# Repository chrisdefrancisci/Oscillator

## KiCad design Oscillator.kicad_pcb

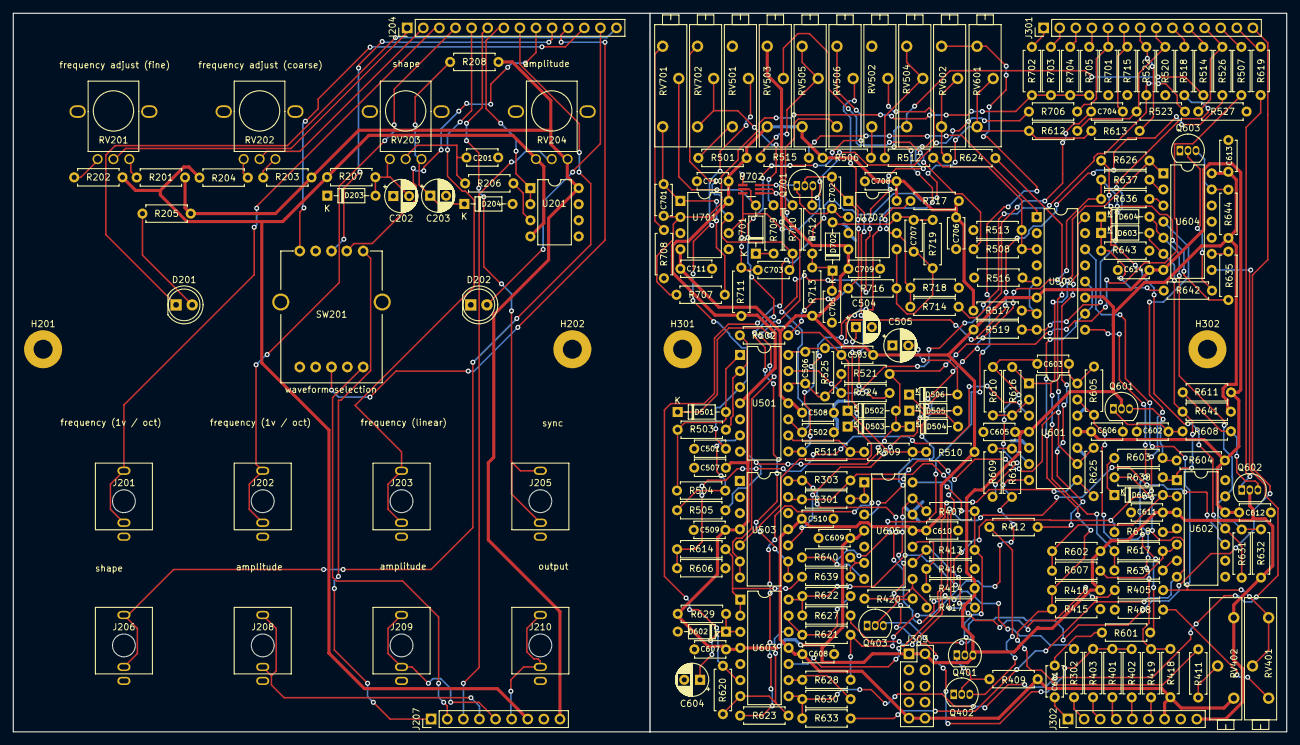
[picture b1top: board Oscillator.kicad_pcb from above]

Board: 2 copper layers, 200.9 x 113.3 mm, 226 parts (0 on the bottom side), 157 nets.

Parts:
C201, C501, C502: .1u; C_Disc_D4.7mm_W2.5mm_P5.00mm
C202, C203, C504, C505, C604: 1u; CP_Radial_D5.0mm_P2.50mm
C503: 0.002u; C_Disc_D4.7mm_W2.5mm_P5.00mm
C506: 10p; C_Disc_D4.7mm_W2.5mm_P5.00mm
C507, C508, C509, C510, C602, C605, C606, C607, C608, C609, C610, C611, C612, C613, C614, C706, C708, C709, C710, C711: 0.1u; C_Disc_D4.7mm_W2.5mm_P5.00mm
C601, C603: 10u; C_Disc_D4.7mm_W2.5mm_P5.00mm
C701, C703, C705: 100p; C_Disc_D4.7mm_W2.5mm_P5.00mm
C702: 0.005u; C_Disc_D4.7mm_W2.5mm_P5.00mm
C704: 0.001u; C_Disc_D4.7mm_W2.5mm_P5.00mm
C707: 4.7p; C_Disc_D4.7mm_W2.5mm_P5.00mm
D201, D202: LED; LED_D5.0mm
D203, D204: NZX5V1B; D_DO-35_SOD27_P7.62mm_Horizontal
D501, D502, D503, D504, D505, D506, D601, D603, D604, D701, D702: D; D_DO-35_SOD27_P7.62mm_Horizontal
D602: BZX55C10; D_DO-35_SOD27_P7.62mm_Horizontal
H201, H202, H301, H302: MountingHole; MountingHole_3mm_Pad
J201, J202, J203, J205, J206, J208, J209, J210: AudioJack2; A-2563
J204, J301: Conn_01x14; PinHeader_1x14_P2.54mm_Vertical
J207, J302: Conn_01x09; PinHeader_1x09_P2.54mm_Vertical
J303: Conn_02x05_Odd_Even; PinHeader_2x05_P2.54mm_Vertical
Q401, Q403, Q603: 2N3904; TO-92_Inline
Q402: 2N3906; TO-92_Inline
Q601, Q602, Q701: Q_NJFET_DSG; TO-92_Inline
R201, R202, R605, R614: 200k; R_Axial_DIN0207_L6.3mm_D2.5mm_P7.62mm_Horizontal
R203, R415, R503, R617, R618, R633, R634, R643: 47k; R_Axial_DIN0207_L6.3mm_D2.5mm_P7.62mm_Horizontal
R204, R206, R207, R208, R502, R504, R505, R506, R509, R522, R523, R524, R602, R626, R627, R629, R632, R639, R640, R641, R644, R710, R716, R717: 10k; R_Axial_DIN0207_L6.3mm_D2.5mm_P7.62mm_Horizontal
R205, R416, R419, R507, R513, R514, R518, R714: 1k; R_Axial_DIN0207_L6.3mm_D2.5mm_P7.62mm_Horizontal
R301, R302, R303, R401, R402, R403, R405, R414, R417, R420, R501, R515, R520, R521, R601, R609, R612, R615, R623, R624, R625, R635, R636, R637, R701, R703, R704, R705, R712, R715: 100k; R_Axial_DIN0207_L6.3mm_D2.5mm_P7.62mm_Horizontal
R407, R413, R707, R718: 2k; R_Axial_DIN0207_L6.3mm_D2.5mm_P7.62mm_Horizontal
R408: 150; R_Axial_DIN0207_L6.3mm_D2.5mm_P7.62mm_Horizontal
R409, R610, R613, R621, R628: 120k; R_Axial_DIN0207_L6.3mm_D2.5mm_P7.62mm_Horizontal
R410, R508: 470k; R_Axial_DIN0207_L6.3mm_D2.5mm_P7.62mm_Horizontal
R411: 2M; R_Axial_DIN0207_L6.3mm_D2.5mm_P7.62mm_Horizontal
R412, R510, R511, R512, R603, R608, R642: 20k; R_Axial_DIN0207_L6.3mm_D2.5mm_P7.62mm_Horizontal
R418, R519, R526, R709: 4.7k; R_Axial_DIN0207_L6.3mm_D2.5mm_P7.62mm_Horizontal
R516: 130k; R_Axial_DIN0207_L6.3mm_D2.5mm_P7.62mm_Horizontal
R517, R604, R611, R702, R706, R711, R719: 1M; R_Axial_DIN0207_L6.3mm_D2.5mm_P7.62mm_Horizontal
R525: 10M; R_Axial_DIN0207_L6.3mm_D2.5mm_P7.62mm_Horizontal
R527, R619: 3k; R_Axial_DIN0207_L6.3mm_D2.5mm_P7.62mm_Horizontal
R606: 180k; R_Axial_DIN0207_L6.3mm_D2.5mm_P7.62mm_Horizontal
R607, R631, R638: 3M; R_Axial_DIN0207_L6.3mm_D2.5mm_P7.62mm_Horizontal
R616, R622, R630: 39k; R_Axial_DIN0207_L6.3mm_D2.5mm_P7.62mm_Horizontal
R620: 33k; R_Axial_DIN0207_L6.3mm_D2.5mm_P7.62mm_Horizontal
R708: 475; R_Axial_DIN0207_L6.3mm_D2.5mm_P7.62mm_Horizontal
R713: 18k; R_Axial_DIN0207_L6.3mm_D2.5mm_P7.62mm_Horizontal
RV201, RV202, RV203, RV204: 100k; A-5513
RV401: 2k; Potentiometer_Bourns_3006P_Horizontal
RV402, RV503, RV504, RV506, RV601, RV602, RV702: 100k; Potentiometer_Bourns_3006P_Horizontal
RV501, RV502: 10k; Potentiometer_Bourns_3006P_Horizontal
RV505: 1M; Potentiometer_Bourns_3006P_Horizontal
RV701: 100; Potentiometer_Bourns_3006P_Horizontal
SW201: SR1712F-0204-20F0A-N9-N-027
U201, U703: TL072; DIP-8_W7.62mm
U501, U503, U601, U603, U605: TL074; DIP-14_W7.62mm
U502: LM13700; DIP-16_W7.62mm
U602: LM339; DIP-14_W7.62mm
U604: 4066; DIP-14_W7.62mm
U701: OP275; DIP-8_W7.62mm
U702: DMMT3904W; SOT-363_SC-70-6_Handsoldering

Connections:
+12V: C507.1, C509.1, C605.1, C607.1, C609.1, C611.1, C613.1, C706.1, C708.1, C710.1, J207.9, J302.9, J303.1, J303.2, Q401.3, Q601.2, Q602.2, R201.1, R203.1, R205.1, R208.2, R410.2, R414.2, R501.1, R506.1, R517.2, R602.2, R629.1, R632.2, R641.2, R644.2, R711.1, R717.1, RV204.3, RV402.1, RV503.1, RV505.1, U201.8, U501.4, U502.11, U503.4, U601.4, U602.3, U603.4, U604.14, U605.4, U701.8, U703.8
-12V: C503.1, C508.2, C510.2, C606.2, C608.2, C610.2, C612.2, C614.2, C709.2, C711.2, J207.7, J302.7, J303.9, J303.10, R202.2, R204.2, R207.2, R409.2, R418.2, R510.1, R519.1, R604.2, R611.1, R713.2, RV204.1, RV402.3, RV503.3, U201.4, U501.11, U502.6, U503.11, U601.11, U602.12, U603.11, U604.7, U605.11, U701.4, U703.4
/main/VCA/CV1: J302.4, R401.2
/main/VCA/CV2: J302.5, R402.2
/main/VCA/IN: R303.1, R405.2, U503.14
/main/VCA/LED: J301.14, Q403.3
/main/VCA/OFFSET: J302.3, R403.2
/main/VCA/OUT: J302.6, R419.1
/main/VCO_RAW/CV1: J301.3, R704.2
/main/VCO_RAW/CV2: J301.4, R705.2
/main/VCO_RAW/CV_LIN: J301.5, R701.1, R706.2
/main/VCO_RAW/OFFSET_COURSE: J301.2, R703.2
/main/VCO_RAW/OFFSET_FINE: J301.1, R702.2
/main/VCO_RAW/RAW: C702.1, Q701.2, R502.2, R716.2, U703.1
/main/VCO_RAW/SYNC_IN: C704.2, J301.6, R715.1
/main/VCO_SHAPE/CV: J301.8, R520.1, R523.2, R612.2
/main/VCO_SHAPE/RAMP: J301.12, R507.1
/main/VCO_SHAPE/SHAPE: J301.7, R522.2, R613.2
/main/VCO_SHAPE/SINE: J301.9, R518.1
/main/VCO_SHAPE/SQUARE: J301.11, R526.2, R527.1
/main/VCO_SHAPE/TRIANGLE: J301.10, R514.1
/main/WAVESHAPER/10v: R614.1, R639.2, U603.1, U603.2
/main/WAVESHAPER/-10v: R640.1, RV601.3, RV602.3, U605.7
/main/WAVESHAPER/High_bias_signal: R618.1, R622.1, R627.2, U603.14, U604.4
/main/WAVESHAPER/IN: C601.2, J302.1
/main/WAVESHAPER/LED: J301.13, R619.1
/main/WAVESHAPER/Low_bias_signal: R630.1, R633.2, U603.8, U604.8
/main/WAVESHAPER/Mid_bias_signal: R616.1, R617.1, R626.2, R634.2, U601.1, U604.1
/main/WAVESHAPER/OUT: R301.2, U605.1, U605.2
/panel/fm_cv1: J201.T, J204.3
/panel/fm_cv2: J202.T, J204.4
/panel/fm_cv_lin: J203.T, J204.5
/panel/fold_led: D202.2, J204.13
/panel/freq_adj_course: J204.2, RV202.2
/panel/freq_adj_fine: J204.1, RV201.2
/panel/out: J207.6, J210.T
/panel/ramp: J204.12, SW201.6
/panel/shape_cv: J204.8, J206.T
/panel/shape_offset: J204.7, U201.1, U201.2
/panel/sine: J204.9, SW201.9
/panel/square: J204.11, SW201.3
/panel/sync: J204.6, J205.T
/panel/tri: J204.10, SW201.8
/panel/vca_cv1: J207.4, J208.T
/panel/vca_cv2: J207.5, J209.T
/panel/vca_led: D201.1, J204.14
/panel/vca_offset: J207.3, RV204.2
/panel/waveshaper_bypass: J207.2, SW201.1
/panel/waveshaper_in: J207.1, SW201.10
GND: C201.2, C202.1, C203.2, C501.2, C502.2, C504.2, C505.1, C507.2, C508.1, C509.2, C510.1, C602.1, C604.2, C605.2, C606.1, C607.2, C608.1, C609.2, C610.1, C611.2, C612.1, C613.2, C614.1, C705.2, C706.2, C708.2, C709.1, C710.2, C711.1, D202.1, D203.1, D204.2, D602.2, J201.S, J202.S, J203.S, J205.S, J206.S, J207.8, J208.S, J209.S, J210.S, J302.8, J303.3, J303.4, J303.5, J303.6, J303.7, J303.8, Q402.1, Q403.1, Q603.1, R408.2, R415.1, R416.1, R513.2, R516.2, R520.2, R527.2, R606.2, R643.1, R701.2, R708.1, R715.2, R718.1, RV501.3, RV502.3, SW201.2, SW201.4, SW201.5, SW201.7, U501.5, U502.4, U502.13, U503.12, U601.5, U601.10, U601.12, U603.5, U605.5, U605.12, U701.3, U701.5, U702.1, U703.3
unnamed: C201.1, R206.2, RV203.2
unnamed: C202.2, D203.2, R207.1, RV203.1
unnamed: C203.1, D204.1, R208.1, RV203.3
unnamed: C501.1, RV501.2, U501.3
unnamed: C502.1, RV502.2, U501.10
unnamed: C503.2, D501.1, D502.1, R509.2, R510.2
unnamed: C504.1, D503.1, U503.5
unnamed: C505.2, D506.2, U503.10
unnamed: C506.1, R525.1, R526.1, U501.14
unnamed: C506.2, R521.1, R525.2, U501.12
unnamed: C601.1, R601.2
unnamed: C602.2, Q601.1, R608.2
unnamed: C603.1, R609.2, R610.2
unnamed: C603.2, R605.1, U601.14
unnamed: C604.1, D602.1, R629.2, U603.3
unnamed: C701.1, R707.1, RV701.1, U701.1
unnamed: C701.2, R702.1, R703.1, R704.1, R705.1, R707.2, U701.2
unnamed: C702.2, Q701.1, U702.6, U703.2
unnamed: C703.1, R710.1, RV702.3, U701.7
unnamed: C703.2, R706.1, R711.2, U701.6, U702.3
unnamed: C704.1, R714.2
unnamed: C705.1, D702.1, R712.1, R713.1
unnamed: C707.1, D702.2, R719.1, U703.7
unnamed: C707.2, R716.1, R719.2, U703.5
unnamed: D201.2, R205.2
unnamed: D501.2, R503.1, R504.1, U501.1
unnamed: D502.2, D503.2, D504.1, R505.1, R507.2, R521.2, U501.7
unnamed: D504.2, D505.1
unnamed: D505.2, D506.1
unnamed: D601.1, R603.1
unnamed: D601.2, R602.1, R607.2, U602.2
unnamed: D603.1, D604.1, R642.1, R643.2
unnamed: D603.2, R638.1, R641.1, U602.1, U604.6
unnamed: D604.2, R631.1, R632.1, U602.13, U604.5
unnamed: D701.1, R709.2
unnamed: D701.2, RV701.2, U702.2
unnamed: J302.2, R302.2
unnamed: Q401.1, Q402.2, R409.1
unnamed: Q401.2, R407.1, R413.2, U605.14
unnamed: Q402.3, R412.1
unnamed: Q403.2, R420.1
unnamed: Q601.3, R603.2, R604.1
unnamed: Q602.1, R619.2
unnamed: Q602.3, R608.1, R611.2
unnamed: Q603.2, R642.2
unnamed: Q603.3, R644.1, U604.13
unnamed: Q701.3, R712.2
unnamed: R201.2, RV201.3
unnamed: R202.1, RV201.1
unnamed: R203.2, RV202.3
unnamed: R204.1, RV202.1
unnamed: R206.1, U201.3
unnamed: R301.1, R302.1, R303.2, U503.13
unnamed: R401.1, R402.1, R403.1, R407.2, U605.13
unnamed: R405.1, RV401.1, RV401.2, U502.14
unnamed: R408.1, RV401.3
unnamed: R410.1, R411.1, R415.2, U502.10, U502.12
unnamed: R411.2, RV402.2
unnamed: R412.2, U502.16
unnamed: R413.1, R417.2, U605.9
unnamed: R414.1, R416.2, U605.10
unnamed: R417.1, R420.2, U605.8
unnamed: R418.1, R419.2, U502.9
unnamed: R501.2, RV501.1
unnamed: R502.1, R503.2, U501.2
unnamed: R504.2, R505.2, U501.6
unnamed: R506.2, RV502.1
unnamed: R508.1, RV503.2
unnamed: R508.2, R512.2, R513.1, U502.3
unnamed: R509.1, R511.2, U501.9
unnamed: R511.1, R514.2, RV504.1, U501.8
unnamed: R512.1, RV504.2, RV504.3
unnamed: R515.1, RV505.2, RV505.3
unnamed: R515.2, U502.1
unnamed: R516.1, R517.1, U502.5, U502.7
unnamed: R518.2, R519.2, U502.8
unnamed: R522.1, R523.1, R524.1, U501.13
unnamed: R524.2, RV506.2
unnamed: R601.1, R605.2, U601.13
unnamed: R606.1, R614.2, U601.3
unnamed: R607.1, R617.2, U602.5
unnamed: R609.1, R615.2, U601.6
unnamed: R610.1, R616.2, U601.2
unnamed: R612.1, R613.1, R620.2, RV601.1, RV601.2, U603.6
unnamed: R615.1, R621.2, R628.2, U601.7
unnamed: R618.2, U602.4
unnamed: R620.1, R623.2, U603.7, U603.12
unnamed: R621.1, R622.2, U603.13
unnamed: R623.1, R624.1, R625.2, U601.9
unnamed: R624.2, RV602.1, RV602.2
unnamed: R625.1, U601.8, U603.10
unnamed: R626.1, R631.2, U602.11
unnamed: R627.1, U602.10
unnamed: R628.1, R630.2, U603.9
unnamed: R633.1, R638.2, U602.7
unnamed: R634.1, U602.6
unnamed: R635.1, R636.1, R637.1, U605.3
unnamed: R635.2, U604.9
unnamed: R636.2, U604.3
unnamed: R637.2, U604.2
unnamed: R639.1, R640.2, U605.6
unnamed: R708.2, RV701.3
unnamed: R709.1, RV702.1, RV702.2
unnamed: R710.2, U702.4, U702.5
unnamed: R714.1, R717.2, R718.2, U703.6
unnamed: RV506.1, U503.6, U503.7
unnamed: RV506.3, U503.8, U503.9

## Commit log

2021-04-13 deleted backup files
2021-04-13 Version control test
2021-04-13 Added version markings
2021-04-13 Added version 1 markings
2021-04-16 Updated for tayda pots A-5513 and jacks A-2563
2021-04-19 Arranging/connecting new knobs/jacks
2021-04-19 deleted extra lm13700
2021-04-19 Routed consolidate lm13700, ran DRC
2021-04-19 Removed extra trace, ran DRC
2021-04-20 Generated updated gerber files
2021-05-07 Increased pads for knob and jack footprints
2021-05-07 Moved junction away from soldering pads of U702
2021-05-26 Began fixing backwards op amp issue
2021-05-26 Documenting op amp issue
2021-05-26 Fixed op amp issue
